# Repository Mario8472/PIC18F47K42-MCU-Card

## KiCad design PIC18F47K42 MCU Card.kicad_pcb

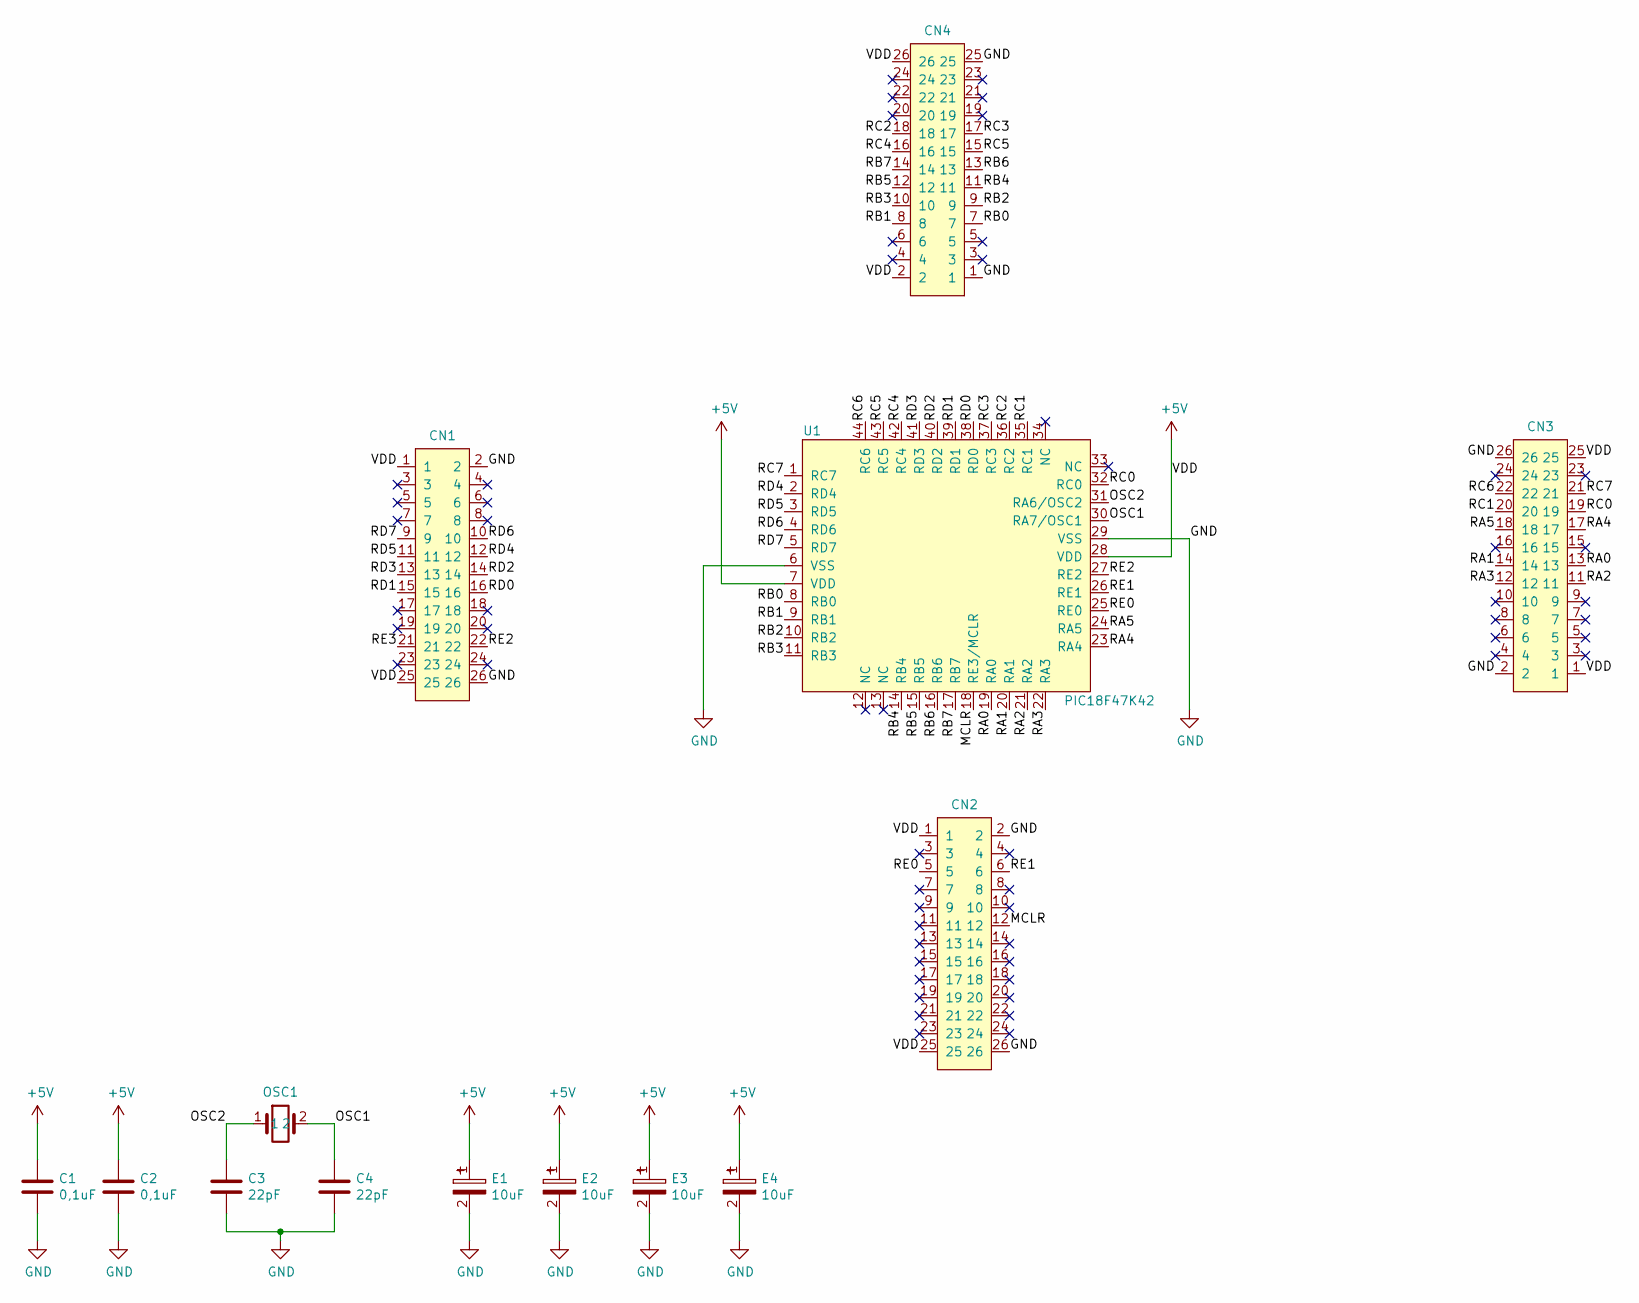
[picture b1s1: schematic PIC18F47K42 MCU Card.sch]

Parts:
C1, C2: 0,1uF; C_0805_2012Metric
C3, C4: 22pF; C_0805_2012Metric
CN1, CN2, CN3, CN4: PinSocket_2x13_2.54mm; SocketPin_2x13_2.54mm
E1, E2, E3, E4: 10uF; CAP_TANTALUM
OSC1: QuartzCrystal_SMD; QuartzCrystal_HC49
U1: PIC18F47K42; TQFP-44_10x10mm_P0.8mm

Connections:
+5V: C1.1, C2.1, CN1.1, CN1.25, CN2.1, CN2.25, CN3.1, CN3.25, CN4.2, CN4.26, E1.1, E2.1, E3.1, E4.1, U1.7 (VDD), U1.28 (VDD)
/MCLR: CN2.12, U1.18 (RE3/MCLR)
/OSC1: C4.1, OSC1.2, U1.30 (RA7/OSC1)
/OSC2: C3.1, OSC1.1, U1.31 (RA6/OSC2)
/RA0: CN3.13, U1.19 (RA0)
/RA1: CN3.14, U1.20 (RA1)
/RA2: CN3.11, U1.21 (RA2)
/RA3: CN3.12, U1.22 (RA3)
/RA4: CN3.17, U1.23 (RA4)
/RA5: CN3.18, U1.24 (RA5)
/RB0: CN4.7, U1.8 (RB0)
/RB1: CN4.8, U1.9 (RB1)
/RB2: CN4.9, U1.10 (RB2)
/RB3: CN4.10, U1.11 (RB3)
/RB4: CN4.11, U1.14 (RB4)
/RB5: CN4.12, U1.15 (RB5)
/RB6: CN4.13, U1.16 (RB6)
/RB7: CN4.14, U1.17 (RB7)
/RC0: CN3.19, U1.32 (RC0)
/RC1: CN3.20, U1.35 (RC1)
/RC2: CN4.18, U1.36 (RC2)
/RC3: CN4.17, U1.37 (RC3)
/RC4: CN4.16, U1.42 (RC4)
/RC5: CN4.15, U1.43 (RC5)
/RC6: CN3.22, U1.44 (RC6)
/RC7: CN3.21, U1.1 (RC7)
/RD0: CN1.16, U1.38 (RD0)
/RD1: CN1.15, U1.39 (RD1)
/RD2: CN1.14, U1.40 (RD2)
/RD3: CN1.13, U1.41 (RD3)
/RD4: CN1.12, U1.2 (RD4)
/RD5: CN1.11, U1.3 (RD5)
/RD6: CN1.10, U1.4 (RD6)
/RD7: CN1.9, U1.5 (RD7)
/RE0: CN2.5, U1.25 (RE0)
/RE1: CN2.6, U1.26 (RE1)
/RE2: CN1.22, U1.27 (RE2)
/RE3: CN1.21
GND: C1.2, C2.2, C3.2, C4.2, CN1.2, CN1.26, CN2.2, CN2.26, CN3.2, CN3.26, CN4.1, CN4.25, E1.2, E2.2, E3.2, E4.2, U1.6 (VSS), U1.29 (VSS)

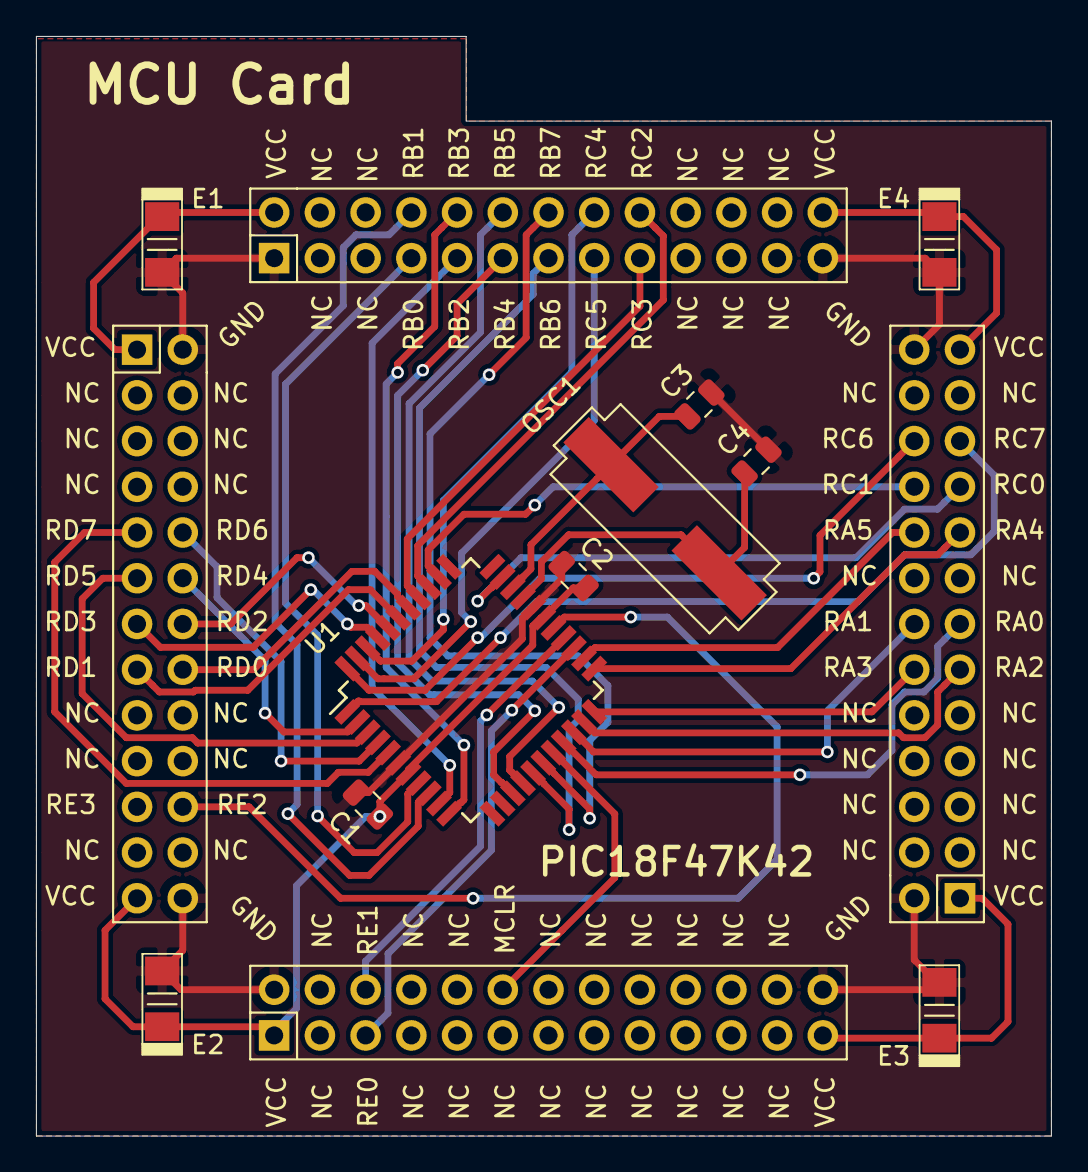
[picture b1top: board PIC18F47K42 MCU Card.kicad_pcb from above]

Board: 2 copper layers, 56.4 x 61.1 mm, 14 parts (0 on the bottom side), 38 nets.

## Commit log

2019-11-15 Create Description
